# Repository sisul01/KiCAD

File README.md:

# KiCAD
My KiCAD projectfolder. It has been created mainly for version management and backup purposes.

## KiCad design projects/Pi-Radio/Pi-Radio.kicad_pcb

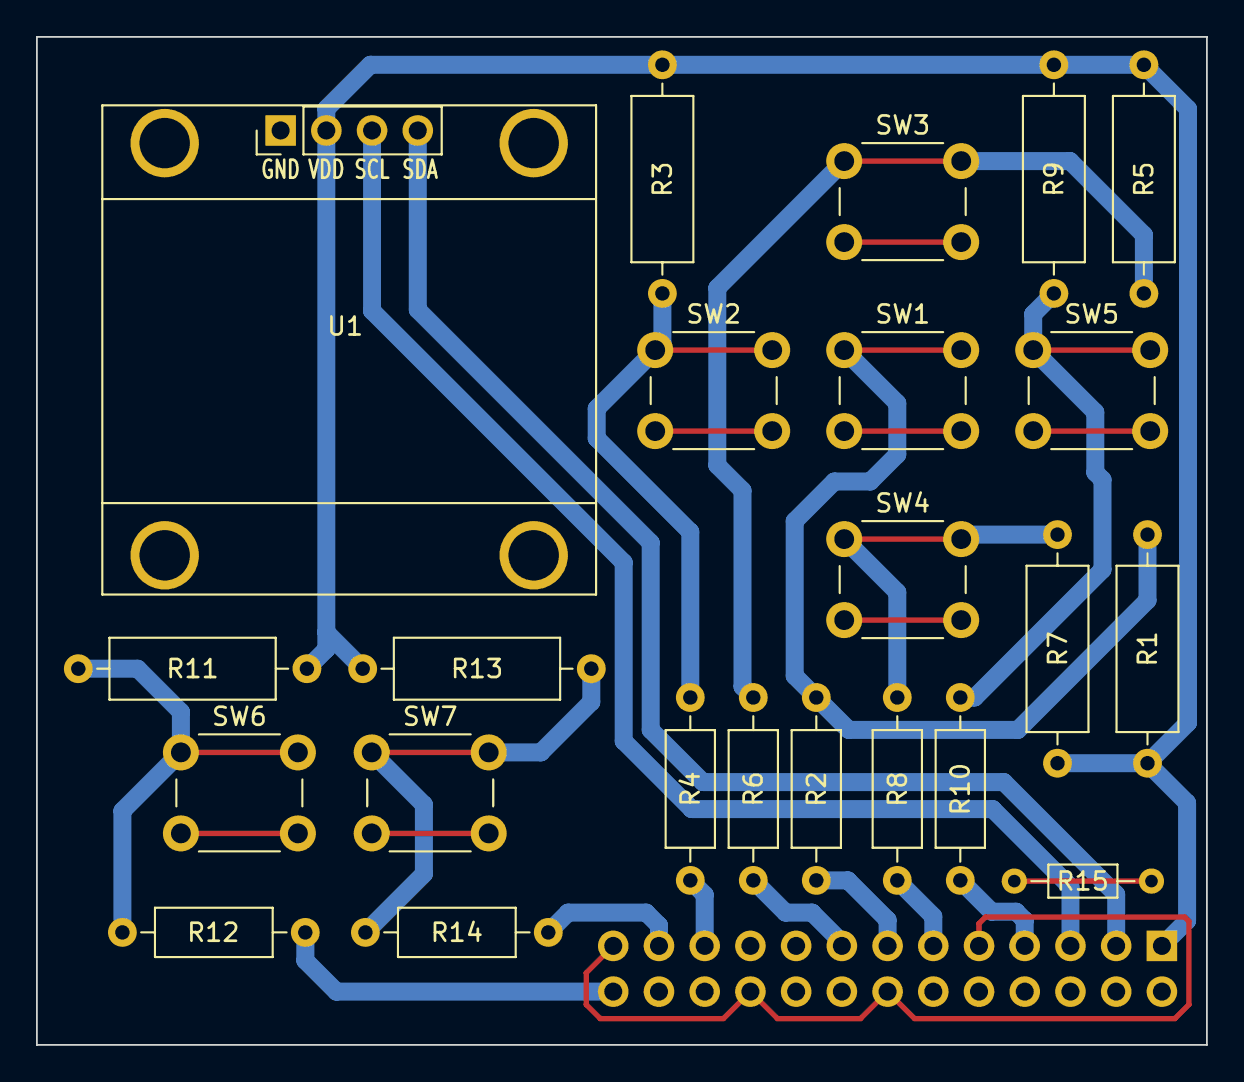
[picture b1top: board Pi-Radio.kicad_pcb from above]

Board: 2 copper layers, 65.0 x 56.0 mm, 24 parts (1 on the bottom side), 18 nets.

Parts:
J1: Conn_02x13_Odd_Even; PinSocket_2x13_P2.54mm_Vertical
R1, R3, R5, R7, R9, R11, R13: 10k; R_Axial_DIN0309_L9.0mm_D3.2mm_P12.70mm_Horizontal
R2, R4, R6, R8, R10, R12, R14: 1k; R_Axial_DIN0207_L6.3mm_D2.5mm_P10.16mm_Horizontal
R15: 0; R_Axial_DIN0204_L3.6mm_D1.6mm_P7.62mm_Horizontal
SW1: Button_PlayStop; SW_PUSH_6mm
SW2: Button_Left; SW_PUSH_6mm
SW3: Button_Up; SW_PUSH_6mm
SW4: Button_Down; SW_PUSH_6mm
SW5: Button_Right; SW_PUSH_6mm
SW6: Button_Time; SW_PUSH_6mm
SW7: Button_Special; SW_PUSH_6mm
U1: Display_OLED_I2C_0.96; Display_128x64_096_I2C

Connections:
+3V3: J1.1, R1.2, R3.2, R5.2, R7.2, R9.2, R11.2, R13.2, U1.2
GND: J1.9, J1.14, J1.20, J1.25, R15.1, R15.2, SW1.2, SW2.2, SW3.2, SW4.2, SW5.2, SW6.2, SW7.2, U1.1
unnamed: R1.1, R2.1, SW1.1
unnamed: R3.1, R4.1, SW2.1
unnamed: R5.1, R6.1, SW3.1
unnamed: R7.1, R8.1, SW4.1
unnamed: R9.1, R10.1, SW5.1
unnamed: R11.1, R12.1, SW6.1
unnamed: R13.1, R14.1, SW7.1
Pin07: J1.7, R10.2
Pin11: J1.11, R8.2
Pin13: J1.13, R2.2
Pin15: J1.15, R6.2
Pin21: J1.21, R4.2
Pin23: J1.23, R14.2
Pin26: J1.26, R12.2
SCL: J1.5, U1.3
SDA: J1.3, U1.4

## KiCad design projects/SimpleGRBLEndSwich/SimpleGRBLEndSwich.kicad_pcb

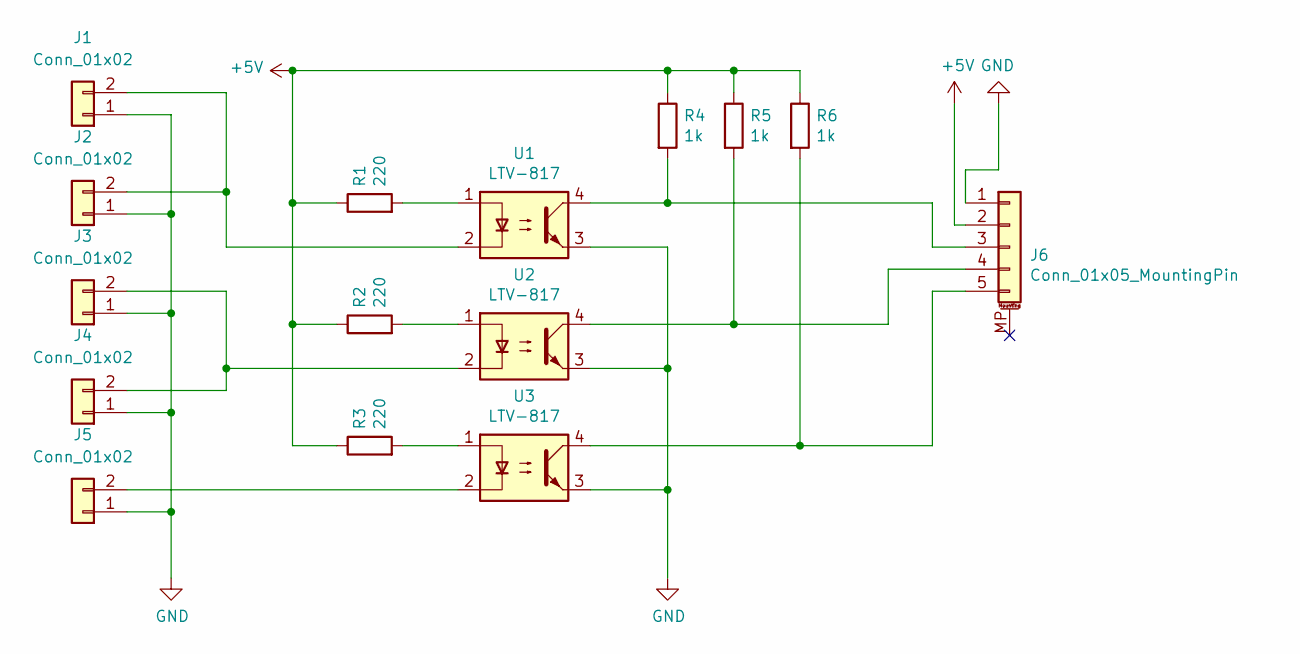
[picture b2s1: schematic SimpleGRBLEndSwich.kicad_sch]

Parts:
J1, J2, J3, J4, J5: Conn_01x02; JST_XH_B2B-XH-A_1x02_P2.50mm_Vertical
J6: Conn_01x05_MountingPin; PinHeader_1x05_P2.54mm_Vertical
R1, R2, R3: 220; R_Axial_DIN0207_L6.3mm_D2.5mm_P7.62mm_Horizontal
R4, R5, R6: 1k; R_Axial_DIN0207_L6.3mm_D2.5mm_P7.62mm_Horizontal
U1, U2, U3: LTV-817; DIP-4_W7.62mm

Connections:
+5V: J6.2, R1.1, R2.1, R3.1, R4.1, R5.1, R6.1
GND: J1.1, J2.1, J3.1, J4.1, J5.1, J6.1, U1.3, U2.3, U3.3
unnamed: J1.2, J2.2, U1.2
unnamed: J3.2, J4.2, U2.2
unnamed: J5.2, U3.2
unnamed: J6.3, R4.2, U1.4
unnamed: J6.4, R5.2, U2.4
unnamed: J6.5, R6.2, U3.4
unnamed: R1.2, U1.1
unnamed: R2.2, U2.1
unnamed: R3.2, U3.1

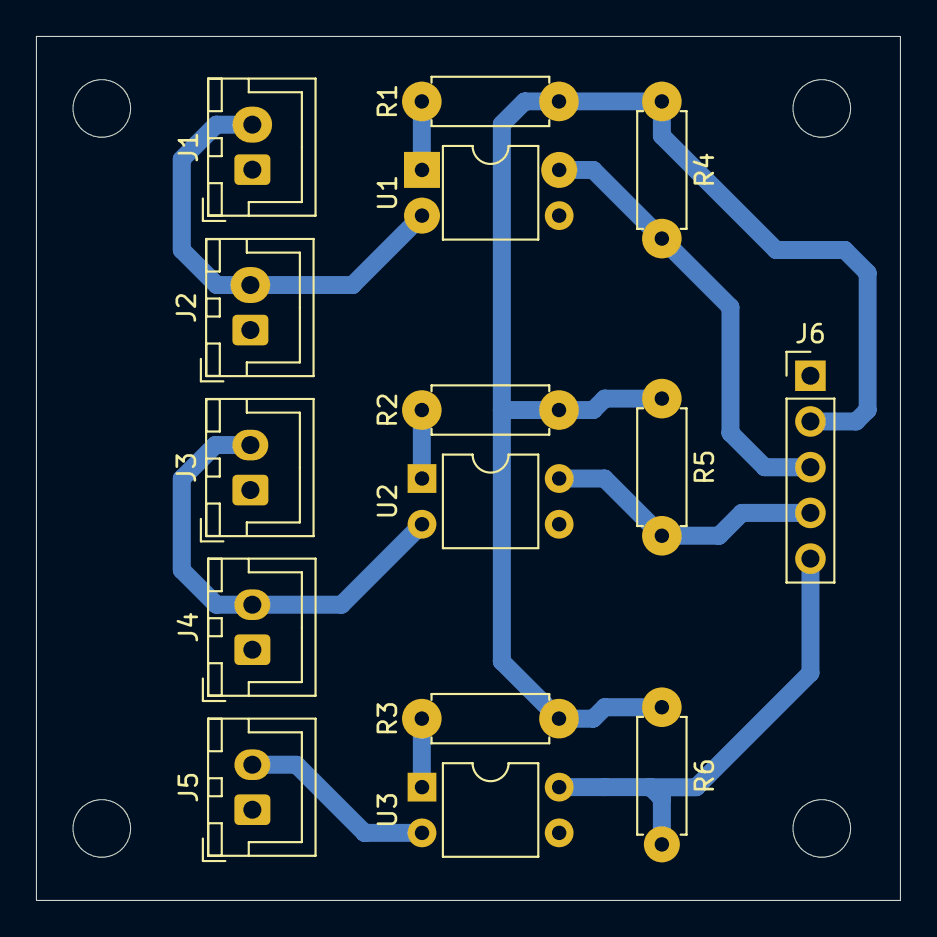
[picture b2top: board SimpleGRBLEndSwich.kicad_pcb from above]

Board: 2 copper layers, 48.0 x 48.0 mm, 15 parts (0 on the bottom side), 11 nets.

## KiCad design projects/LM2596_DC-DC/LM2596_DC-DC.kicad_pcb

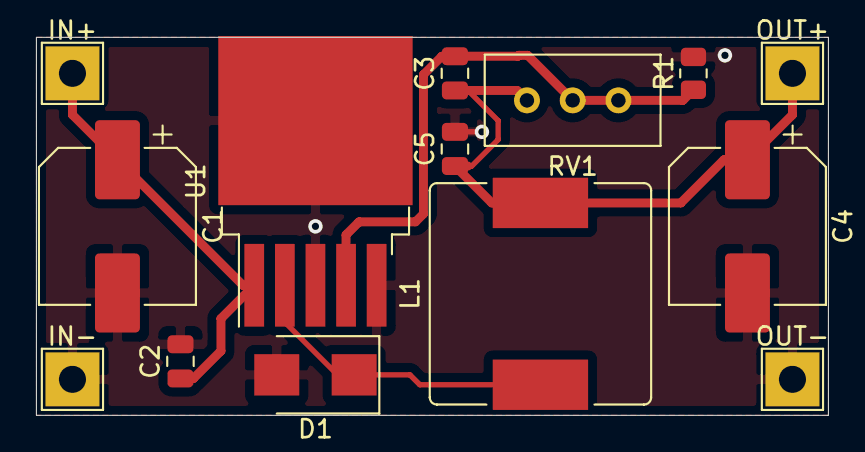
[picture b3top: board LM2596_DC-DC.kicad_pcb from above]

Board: 2 copper layers, 44.0 x 21.0 mm, 14 parts (0 on the bottom side), 5 nets.

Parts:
C1, C4: 220 uF; CP_Elec_8x10.5
C2, C5: 0.1uF; C_0805_2012Metric
C3: 3300pF; C_0805_2012Metric
D1: SK34; D_SMB
IN+: IN+; TestPoint_THTPad_3.0x3.0mm_Drill1.5mm
IN-: IN-; TestPoint_THTPad_3.0x3.0mm_Drill1.5mm
L1: 68uH; L_Bourns_SRR1210A
OUT+: OUT+; TestPoint_THTPad_3.0x3.0mm_Drill1.5mm
OUT-: OUT-; TestPoint_THTPad_3.0x3.0mm_Drill1.5mm
R1: 1K; R_0805_2012Metric
RV1: 10k; Potentiometer_Bourns_3296W_Vertical
U1: LM2596S-ADJ; TO-263-5_TabPin3

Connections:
GND: C1.2, C2.2, C4.2, C5.2, D1.2, IN-.1, OUT-.1, R1.2, U1.3, U1.5
unnamed: C1.1, C2.1, IN+.1, U1.1
unnamed: C3.1, C4.1, C5.1, L1.2, OUT+.1, RV1.1
unnamed: C3.2, R1.1, RV1.2, RV1.3, U1.4
unnamed: D1.1, L1.1, U1.2

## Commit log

2021-10-31 readme files added
